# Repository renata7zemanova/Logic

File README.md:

# Elektronická hra Logic

Elektronická hra Logic je hra, která je založena na principu deskové hry Logic.

## DPS

Deska plošného spoje je nakreslena v programu KiCad. 

## Software

Pro programování DPS Elektronické hry Logic je zapotřebí stáhnout a nainstalovat vývojové prostředí [Visual Studio Code](https://code.visualstudio.com/) a v něm rozšíření PlatformIO. 

Software je napsán pomocí Arduino frameworku.

Při programování musí být přepínač SW15 vždy dole (v pozici 1).

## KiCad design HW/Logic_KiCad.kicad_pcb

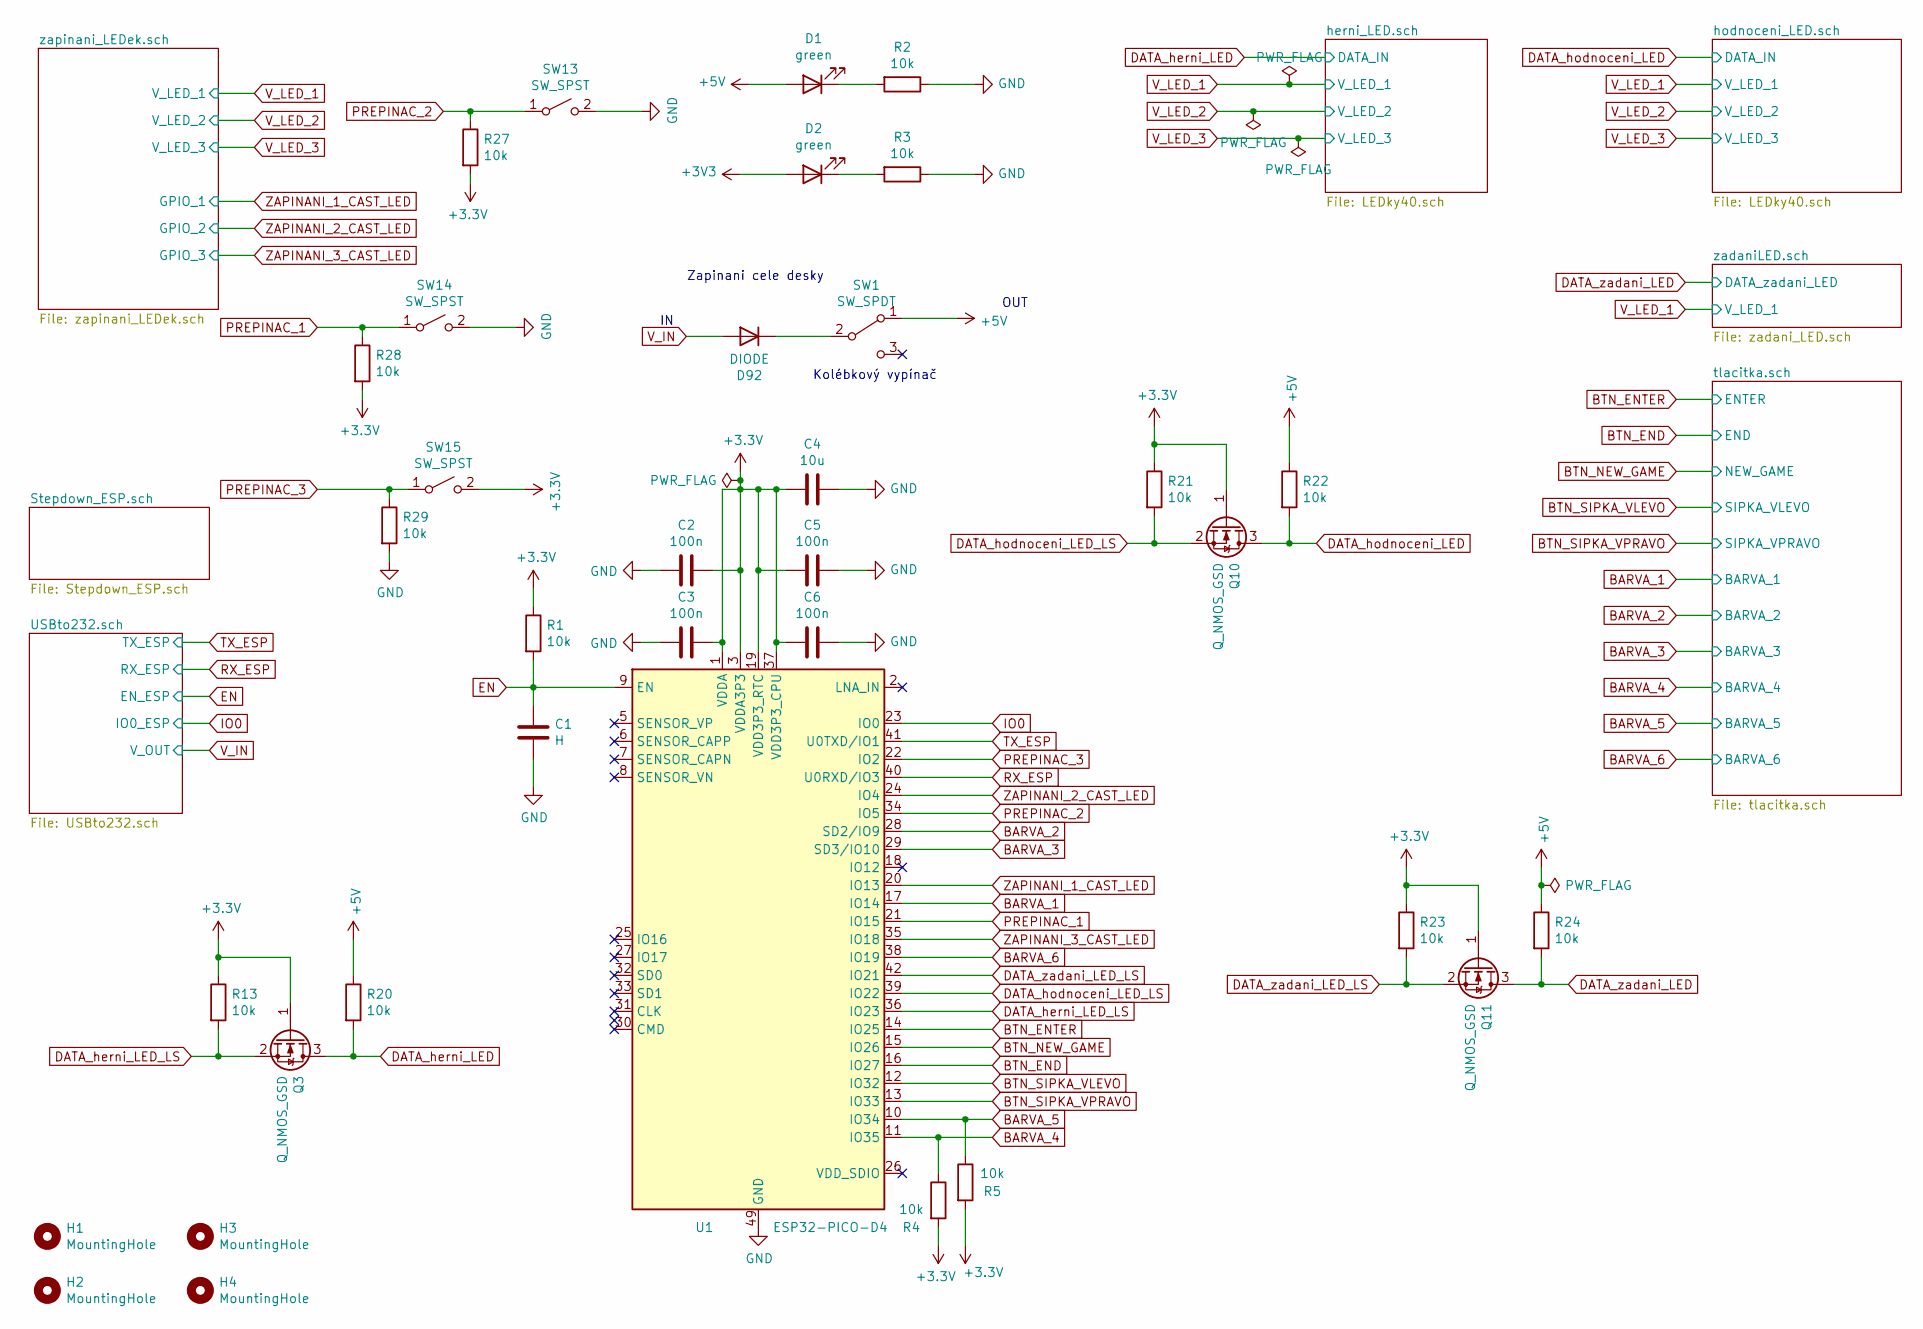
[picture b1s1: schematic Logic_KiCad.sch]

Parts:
C1: H; C_0402_1005Metric; LCSC C52923
C2, C3, C5, C6: 100n; C_0402_1005Metric; LCSC C1525
C4: 10u; C_0402_1005Metric; LCSC C15525
D1, D2: green; LED_0603_1608Metric; LCSC C72043
D92: DIODE; D_SMA; LCSC C8678
H1, H2, H3, H4: MountingHole; MountingHole_3.2mm_M3_DIN965_Pad; JLCPCB_CORRECTION 0;0;0
Q3, Q10, Q11: Q_NMOS_GSD; SOT-23; LCSC C8545
R1, R2, R3, R4, R5, R13, R20, R21, R22, R23, R24, R27, R28, R29: 10k; R_0402_1005Metric; LCSC C25744
SW1: SW_SPDT; PinHeader_1x03_P2.54mm_Vertical; LCSC ručně
SW13: SW_SPST; DIP1x1; JLCPCB_CORRECTION 0;0;270
SW14, SW15: SW_SPST; DIP1x1; JLCPCB_CORRECTION 0;0;90
U1: ESP32-PICO-D4; QFN-48-1EP_7x7mm_P0.5mm_EP5.3x5.3mm; LCSC C193707

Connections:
+5V: D1.2 (A), R20.1, R22.1, R24.1, SW1.1 (A); also elsewhere on the board
BARVA_1: U1.17 (IO14); also elsewhere on the board
BARVA_2: U1.28 (SD2/IO9); also elsewhere on the board
BARVA_3: U1.29 (SD3/IO10); also elsewhere on the board
BARVA_4: R4.1, U1.11 (IO35); also elsewhere on the board
BARVA_5: R5.1, U1.10 (IO34); also elsewhere on the board
BARVA_6: U1.38 (IO19); also elsewhere on the board
BTN_END: U1.16 (IO27); also elsewhere on the board
BTN_ENTER: U1.14 (IO25); also elsewhere on the board
BTN_NEW_GAME: U1.15 (IO26); also elsewhere on the board
BTN_SIPKA_VLEVO: U1.12 (IO32); also elsewhere on the board
BTN_SIPKA_VPRAVO: U1.13 (IO33); also elsewhere on the board
DATA_herni_LED: Q3.3 (D), R20.2; also elsewhere on the board
DATA_herni_LED_LS: Q3.2 (S), R13.2, U1.36 (IO23)
DATA_hodnoceni_LED: Q10.3 (D), R22.2; also elsewhere on the board
DATA_hodnoceni_LED_LS: Q10.2 (S), R21.2, U1.39 (IO22)
DATA_zadani_LED: Q11.3 (D), R24.2; also elsewhere on the board
DATA_zadani_LED_LS: Q11.2 (S), R23.2, U1.42 (IO21)
EN: C1.2, R1.2, U1.9 (EN); also elsewhere on the board
GND: C1.1, C2.2, C3.2, C4.1, C5.1, C6.1, R2.1, R3.1, R29.2, SW13.2 (B), SW14.2 (B), U1.49 (GND); also elsewhere on the board
IO0: U1.23 (IO0); also elsewhere on the board
unnamed: D1.1 (K), R2.2
unnamed: D2.1 (K), R3.2
unnamed: D92.1 (K), SW1.2 (B)
PREPINAC_1: R28.1, SW14.1 (A), U1.21 (IO15)
PREPINAC_2: R27.1, SW13.1 (A), U1.34 (IO5)
PREPINAC_3: R29.1, SW15.1 (A), U1.22 (IO2)
RX_ESP: U1.40 (U0RXD/IO3); also elsewhere on the board
TX_ESP: U1.41 (U0TXD/IO1); also elsewhere on the board
V_IN: D92.2 (A); also elsewhere on the board
ZAPINANI_1_CAST_LED: U1.20 (IO13); also elsewhere on the board
ZAPINANI_2_CAST_LED: U1.24 (IO4); also elsewhere on the board
ZAPINANI_3_CAST_LED: U1.35 (IO18); also elsewhere on the board

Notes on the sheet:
Zapinani cele desky
Kolébkový vypínač
OUT

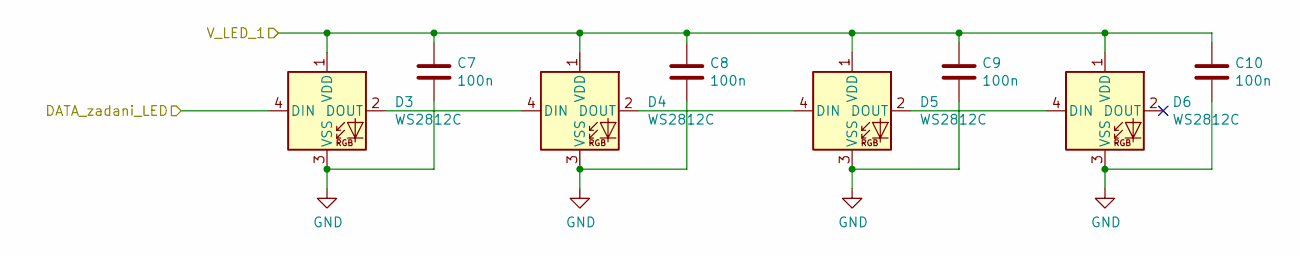
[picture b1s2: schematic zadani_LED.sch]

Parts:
C7, C8, C9, C10: 100n; C_0402_1005Metric; LCSC C1525
D3, D4, D5, D6: WS2812C; LED_WS2812B_PLCC4_5.0x5.0mm_P3.2mm; LCSC C114587

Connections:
DATA_zadani_LED: D3.4 (DIN); also elsewhere on the board
GND: C7.2, C8.2, C9.2, C10.2, D3.3 (VSS), D4.3 (VSS), D5.3 (VSS), D6.3 (VSS); also elsewhere on the board
unnamed: D3.2 (DOUT), D4.4 (DIN)
unnamed: D4.2 (DOUT), D5.4 (DIN)
unnamed: D5.2 (DOUT), D6.4 (DIN)
V_LED_1: C7.1, C8.1, C9.1, C10.1, D3.1 (VDD), D4.1 (VDD), D5.1 (VDD), D6.1 (VDD); also elsewhere on the board

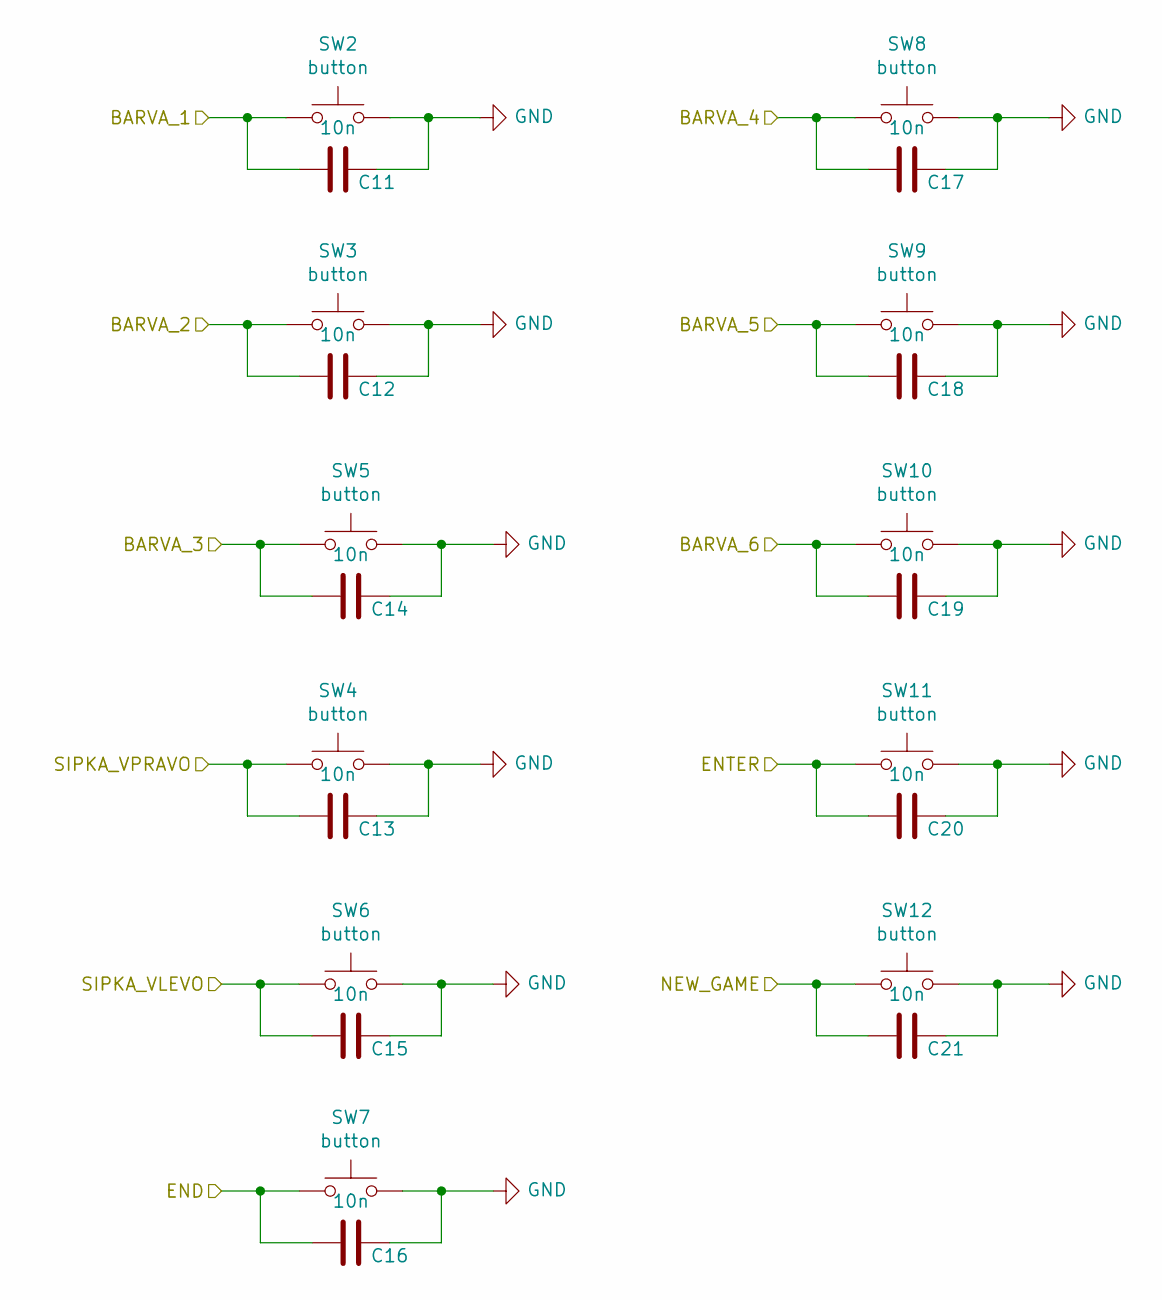
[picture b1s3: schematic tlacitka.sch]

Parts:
C11, C12, C13, C14, C15, C16, C17, C18, C19, C20, C21: 10n; C_0402_1005Metric; LCSC C15195
SW2, SW3, SW4, SW5, SW6, SW7, SW8, SW9, SW10, SW11, SW12: button; Tactile_switch; LCSC C318886

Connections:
BARVA_1: C11.2, SW2.1; also elsewhere on the board
BARVA_2: C12.2, SW3.1; also elsewhere on the board
BARVA_3: C14.2, SW5.1; also elsewhere on the board
BARVA_4: C17.2, SW8.1; also elsewhere on the board
BARVA_5: C18.2, SW9.1; also elsewhere on the board
BARVA_6: C19.2, SW10.1; also elsewhere on the board
BTN_END: C16.2, SW7.1; also elsewhere on the board
BTN_ENTER: C20.2, SW11.1; also elsewhere on the board
BTN_NEW_GAME: C21.2, SW12.1; also elsewhere on the board
BTN_SIPKA_VLEVO: C15.2, SW6.1; also elsewhere on the board
BTN_SIPKA_VPRAVO: C13.2, SW4.1; also elsewhere on the board
GND: C11.1, C12.1, C13.1, C14.1, C15.1, C16.1, C17.1, C18.1, C19.1, C20.1, C21.1, SW2.2, SW3.2, SW4.2, SW5.2, SW6.2, SW7.2, SW8.2, SW9.2, SW10.2, SW11.2, SW12.2; also elsewhere on the board

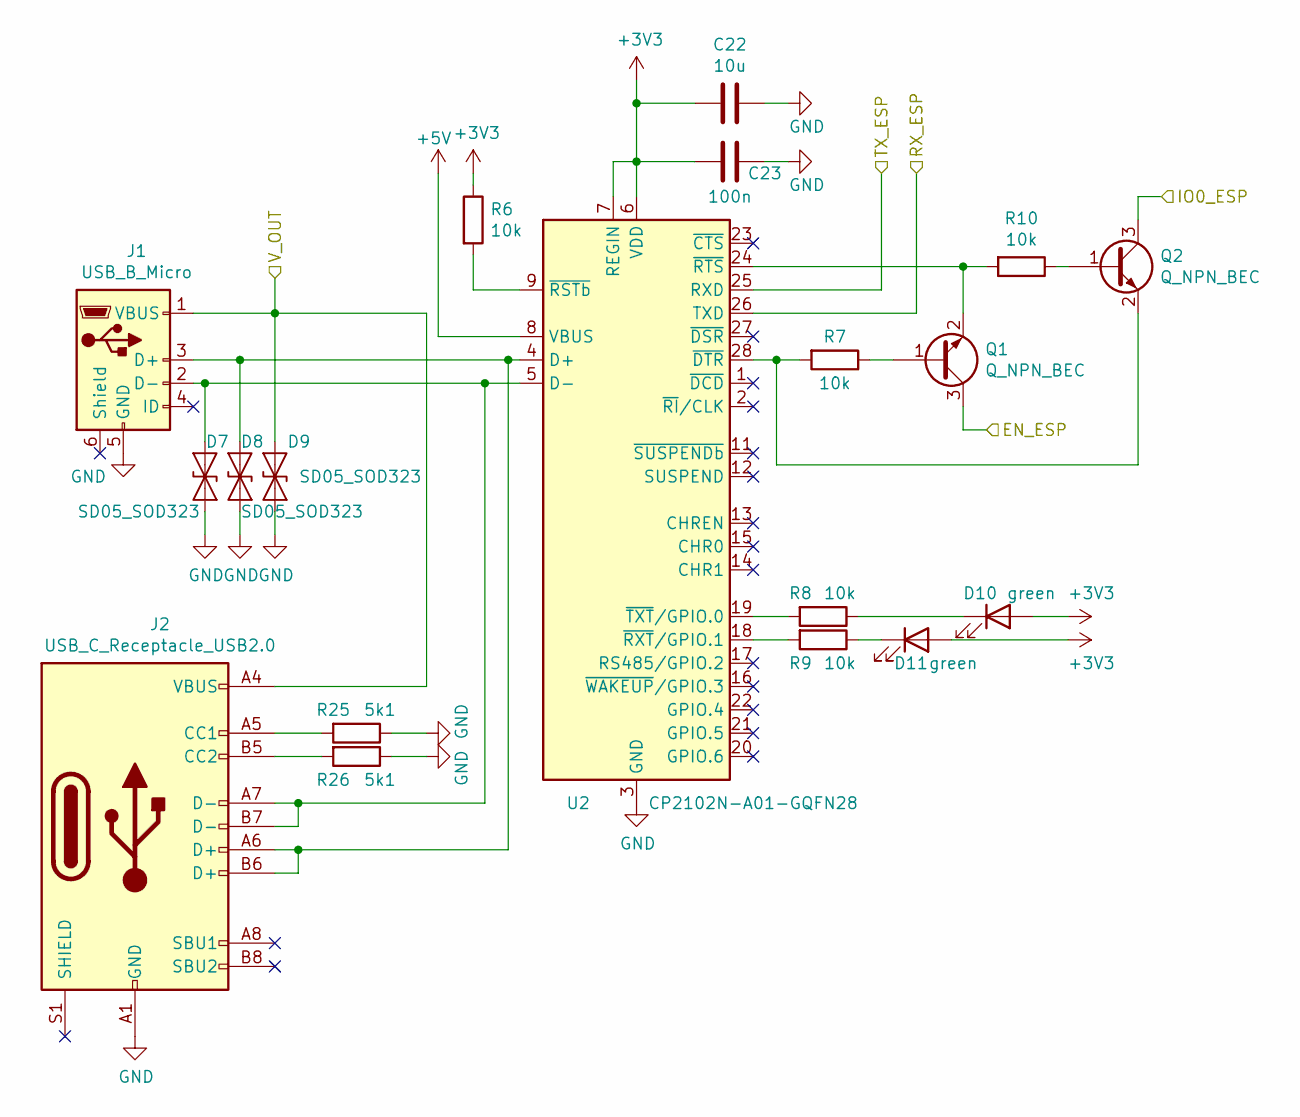
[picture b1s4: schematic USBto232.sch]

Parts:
C22: 10u; C_0402_1005Metric; LCSC C15525
C23: 100n; C_0402_1005Metric; LCSC C1525
D7, D8, D9: SD05_SOD323; D_SOD-323; LCSC neosazovat
D10, D11: green; LED_0603_1608Metric; LCSC C72043
J1: USB_B_Micro; USB_Micro-B_Wuerth_629105150521; LCSC C319164
J2: USB_C_Receptacle_USB2.0; USB_C_Receptacle_HRO_TYPE-C-31-M-12; JLCPCB_CORRECTION 1.8;0;180
Q1, Q2: Q_NPN_BEC; SOT-23; LCSC C20526
R6, R7, R8, R9, R10: 10k; R_0402_1005Metric; LCSC C25744
R25, R26: 5k1; R_0402_1005Metric; JLCPCB_CORRECTION 0;0;0
U2: CP2102N-A01-GQFN28; QFN-28-1EP_5x5mm_P0.5mm_EP3.35x3.35mm; LCSC C6568

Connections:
+5V: U2.8 (VBUS); also elsewhere on the board
EN: Q1.3 (C); also elsewhere on the board
GND: C22.1, C23.1, D7.1 (A1), D8.1 (A1), D9.1 (A1), J1.5 (GND), J2.A1 (GND), J2.A12 (GND), J2.B1 (GND), J2.B12 (GND), R25.1, R26.1, U2.3 (GND), U2.29 (GND); also elsewhere on the board
IO0: Q2.3 (C); also elsewhere on the board
unnamed: D7.2 (A2), J1.2 (D-), J2.A7 (D-), J2.B7 (D-), U2.5 (D-)
unnamed: D8.2 (A2), J1.3 (D+), J2.A6 (D+), J2.B6 (D+), U2.4 (D+)
unnamed: D10.1 (K), R8.1
unnamed: D11.1 (K), R9.1
unnamed: J2.A5 (CC1), R25.2
unnamed: J2.B5 (CC2), R26.2
unnamed: Q1.1 (B), R7.1
unnamed: Q1.2 (E), R10.2, U2.24 (~RTS)
unnamed: Q2.1 (B), R10.1
unnamed: Q2.2 (E), R7.2, U2.28 (~DTR)
unnamed: R6.2, U2.9 (~RSTb)
unnamed: R8.2, U2.19 (~TXT~/GPIO.0)
unnamed: R9.2, U2.18 (~RXT~/GPIO.1)
RX_ESP: U2.26 (TXD); also elsewhere on the board
TX_ESP: U2.25 (RXD); also elsewhere on the board
V_IN: D9.2 (A2), J1.1 (VBUS), J2.A4 (VBUS), J2.A9 (VBUS), J2.B4 (VBUS), J2.B9 (VBUS); also elsewhere on the board

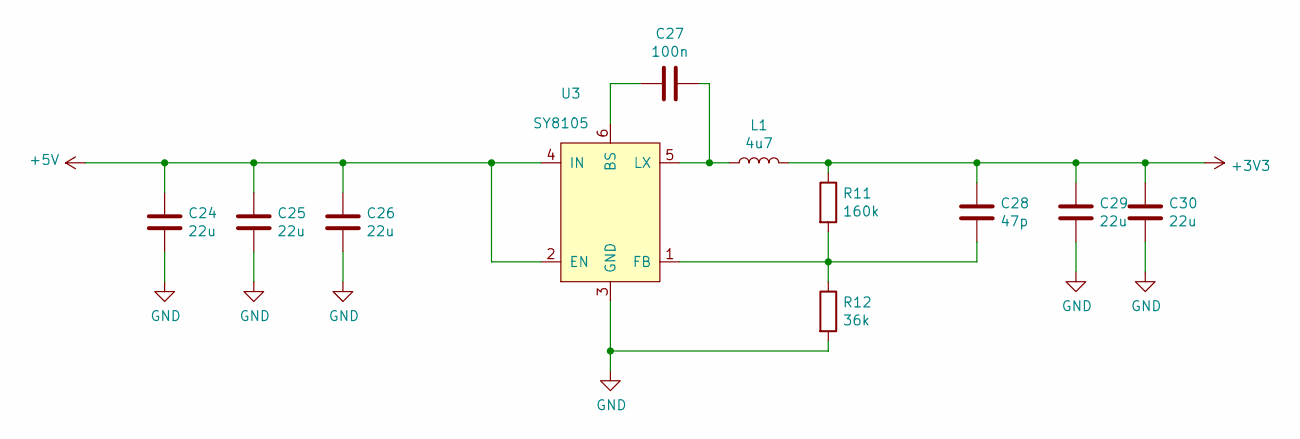
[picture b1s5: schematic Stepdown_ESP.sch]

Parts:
C24, C25, C26, C29, C30: 22u; C_0603_1608Metric; LCSC C59461
C27: 100n; C_0402_1005Metric; LCSC C1525
C28: 47p; C_0402_1005Metric; LCSC C1567
L1: 4u7; MWSA0503S; LCSC C408410
R11: 160k; R_0603_1608Metric; LCSC C22813
R12: 36k; R_0603_1608Metric; LCSC C23147
U3: SY8105; TSOT-23-6; LCSC C178247

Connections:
+5V: C24.1, C25.1, C26.1, U3.2 (EN), U3.4 (IN); also elsewhere on the board
GND: C24.2, C25.2, C26.2, C29.1, C30.1, R12.2, U3.3 (GND); also elsewhere on the board
unnamed: C27.1, L1.1, U3.5 (LX)
unnamed: C27.2, U3.6 (BS)
unnamed: C28.1, R11.2, R12.1, U3.1 (FB)

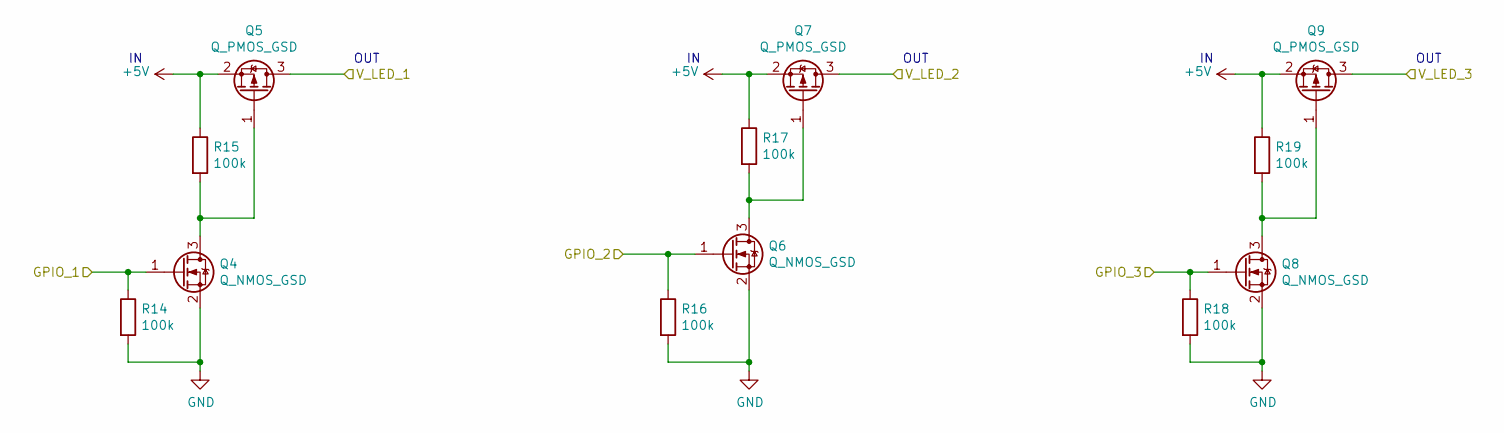
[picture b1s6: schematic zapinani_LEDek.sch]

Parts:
Q4, Q6, Q8: Q_NMOS_GSD; SOT-23; LCSC C8545
Q5, Q7, Q9: Q_PMOS_GSD; SOT-23; LCSC C10487
R14, R15, R16, R17, R18, R19: 100k; R_0402_1005Metric; LCSC C25741

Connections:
+5V: Q5.2 (S), Q7.2 (S), Q9.2 (S), R15.1, R17.1, R19.1; also elsewhere on the board
GND: Q4.2 (S), Q6.2 (S), Q8.2 (S), R14.2, R16.2, R18.2; also elsewhere on the board
unnamed: Q4.3 (D), Q5.1 (G), R15.2
unnamed: Q6.3 (D), Q7.1 (G), R17.2
unnamed: Q8.3 (D), Q9.1 (G), R19.2
V_LED_1: Q5.3 (D); also elsewhere on the board
V_LED_2: Q7.3 (D); also elsewhere on the board
V_LED_3: Q9.3 (D); also elsewhere on the board
ZAPINANI_1_CAST_LED: Q4.1 (G), R14.1; also elsewhere on the board
ZAPINANI_2_CAST_LED: Q6.1 (G), R16.1; also elsewhere on the board
ZAPINANI_3_CAST_LED: Q8.1 (G), R18.1; also elsewhere on the board

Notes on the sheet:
OUT

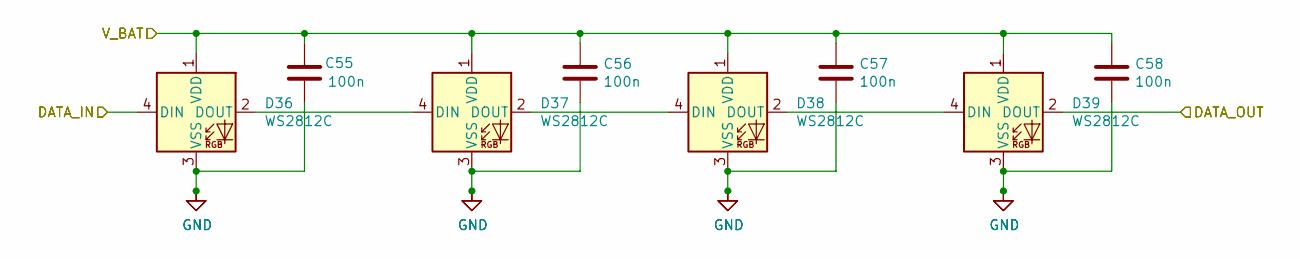
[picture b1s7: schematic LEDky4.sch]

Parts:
C75, C76, C77, C78: 100n; C_0402_1005Metric; LCSC C1525
D56, D57, D58, D59: WS2812C; LED_WS2812B_PLCC4_5.0x5.0mm_P3.2mm; LCSC C114587

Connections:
/hodnoceni_LED.sch/2.sch/DATA_IN: D56.4 (DIN); also elsewhere on the board
/hodnoceni_LED.sch/3.sch/DATA_IN: D59.2 (DOUT); also elsewhere on the board
GND: C75.2, C76.2, C77.2, C78.2, D56.3 (VSS), D57.3 (VSS), D58.3 (VSS), D59.3 (VSS); also elsewhere on the board
unnamed: D56.2 (DOUT), D57.4 (DIN)
unnamed: D57.2 (DOUT), D58.4 (DIN)
unnamed: D58.2 (DOUT), D59.4 (DIN)
V_LED_1: C75.1, C76.1, C77.1, C78.1, D56.1 (VDD), D57.1 (VDD), D58.1 (VDD), D59.1 (VDD); also elsewhere on the board

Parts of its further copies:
C31, C32, C33, C34, C35, C36, C37, C38, C39, C40, C41, C42, C43, C44, C45, C46, C47, C48, C49, C50, C51, C52, C53, C54, C55, C56, C57, C58, C59, C60, C61, C62, C63, C64, C65, C66, C67, C68, C69, C70, C71, C72, C73, C74, C79, C80, C81, C82, C83, C84, C85, C86, C87, C88, C89, C90, C91, C92, C93, C94, C95, C96, C97, C98, C99, C100, C101, C102, C103, C104, C105, C106, C107, C108, C109, C110: 100n; C_0402_1005Metric; LCSC C1525
D12, D13, D14, D15, D16, D17, D18, D19, D20, D21, D22, D23, D24, D25, D26, D27, D28, D29, D30, D31, D32, D33, D34, D35, D36, D37, D38, D39, D40, D41, D42, D43, D44, D45, D46, D47, D48, D49, D50, D51, D52, D53, D54, D55, D60, D61, D62, D63, D64, D65, D66, D67, D68, D69, D70, D71, D72, D73, D74, D75, D76, D77, D78, D79, D80, D81, D82, D83, D84, D85, D86, D87, D88, D89, D90, D91: WS2812C; LED_WS2812B_PLCC4_5.0x5.0mm_P3.2mm; LCSC C114587

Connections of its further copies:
/herni_LED.sch/2.sch/DATA_IN: D15.2 (DOUT), D16.4 (DIN)
/herni_LED.sch/3.sch/DATA_IN: D19.2 (DOUT), D20.4 (DIN)
/herni_LED.sch/4.ch/DATA_IN: D23.2 (DOUT), D24.4 (DIN)
/herni_LED.sch/5.sch/DATA_IN: D27.2 (DOUT), D28.4 (DIN)
/herni_LED.sch/6.sch/DATA_IN: D31.2 (DOUT), D32.4 (DIN)
/herni_LED.sch/7.sch/DATA_IN: D35.2 (DOUT), D36.4 (DIN)
/herni_LED.sch/8.sch/DATA_IN: D39.2 (DOUT), D40.4 (DIN)
/herni_LED.sch/9.sch/DATA_IN: D43.2 (DOUT), D44.4 (DIN)
/herni_LED.sch/10.sch/DATA_IN: D47.2 (DOUT), D48.4 (DIN)
/herni_LED.sch/10.sch/DATA_OUT: D51.2 (DOUT)
/hodnoceni_LED.sch/2.sch/DATA_IN: D55.2 (DOUT); also elsewhere on the board
/hodnoceni_LED.sch/3.sch/DATA_IN: D60.4 (DIN); also elsewhere on the board
/hodnoceni_LED.sch/4.ch/DATA_IN: D63.2 (DOUT), D64.4 (DIN)
/hodnoceni_LED.sch/5.sch/DATA_IN: D67.2 (DOUT), D68.4 (DIN)
/hodnoceni_LED.sch/6.sch/DATA_IN: D71.2 (DOUT), D72.4 (DIN)
/hodnoceni_LED.sch/7.sch/DATA_IN: D75.2 (DOUT), D76.4 (DIN)
/hodnoceni_LED.sch/8.sch/DATA_IN: D79.2 (DOUT), D80.4 (DIN)
/hodnoceni_LED.sch/9.sch/DATA_IN: D83.2 (DOUT), D84.4 (DIN)
/hodnoceni_LED.sch/10.sch/DATA_IN: D87.2 (DOUT), D88.4 (DIN)
/hodnoceni_LED.sch/10.sch/DATA_OUT: D91.2 (DOUT)
DATA_herni_LED: D12.4 (DIN); also elsewhere on the board
DATA_hodnoceni_LED: D52.4 (DIN); also elsewhere on the board
GND: C31.2, C32.2, C33.2, C34.2, C35.2, C36.2, C37.2, C38.2, C39.2, C40.2, C41.2, C42.2, C43.2, C44.2, C45.2, C46.2, C47.2, C48.2, C49.2, C50.2, C51.2, C52.2, C53.2, C54.2, C55.2, C56.2, C57.2, C58.2, C59.2, C60.2, C61.2, C62.2, C63.2, C64.2, C65.2, C66.2, C67.2, C68.2, C69.2, C70.2, C71.2, C72.2, C73.2, C74.2, C79.2, C80.2, C81.2, C82.2, C83.2, C84.2, C85.2, C86.2, C87.2, C88.2, C89.2, C90.2, C91.2, C92.2, C93.2, C94.2, C95.2, C96.2, C97.2, C98.2, C99.2, C100.2, C101.2, C102.2, C103.2, C104.2, C105.2, C106.2, C107.2, C108.2, C109.2, C110.2, D12.3 (VSS), D13.3 (VSS), D14.3 (VSS), D15.3 (VSS), D16.3 (VSS), D17.3 (VSS), D18.3 (VSS), D19.3 (VSS), D20.3 (VSS), D21.3 (VSS), D22.3 (VSS), D23.3 (VSS), D24.3 (VSS), D25.3 (VSS), D26.3 (VSS), D27.3 (VSS), D28.3 (VSS), D29.3 (VSS), D30.3 (VSS), D31.3 (VSS), D32.3 (VSS), D33.3 (VSS), D34.3 (VSS), D35.3 (VSS), D36.3 (VSS), D37.3 (VSS), D38.3 (VSS), D39.3 (VSS), D40.3 (VSS), D41.3 (VSS), D42.3 (VSS), D43.3 (VSS), D44.3 (VSS), D45.3 (VSS), D46.3 (VSS), D47.3 (VSS), D48.3 (VSS), D49.3 (VSS), D50.3 (VSS), D51.3 (VSS), D52.3 (VSS), D53.3 (VSS), D54.3 (VSS), D55.3 (VSS), D60.3 (VSS), D61.3 (VSS), D62.3 (VSS), D63.3 (VSS), D64.3 (VSS), D65.3 (VSS), D66.3 (VSS), D67.3 (VSS), D68.3 (VSS), D69.3 (VSS), D70.3 (VSS), D71.3 (VSS), D72.3 (VSS), D73.3 (VSS), D74.3 (VSS), D75.3 (VSS), D76.3 (VSS), D77.3 (VSS), D78.3 (VSS), D79.3 (VSS), D80.3 (VSS), D81.3 (VSS), D82.3 (VSS), D83.3 (VSS), D84.3 (VSS), D85.3 (VSS), D86.3 (VSS), D87.3 (VSS), D88.3 (VSS), D89.3 (VSS), D90.3 (VSS), D91.3 (VSS); also elsewhere on the board
unnamed: D12.2 (DOUT), D13.4 (DIN)
unnamed: D13.2 (DOUT), D14.4 (DIN)
unnamed: D14.2 (DOUT), D15.4 (DIN)
unnamed: D16.2 (DOUT), D17.4 (DIN)
unnamed: D17.2 (DOUT), D18.4 (DIN)
unnamed: D18.2 (DOUT), D19.4 (DIN)
unnamed: D20.2 (DOUT), D21.4 (DIN)
unnamed: D21.2 (DOUT), D22.4 (DIN)
unnamed: D22.2 (DOUT), D23.4 (DIN)
unnamed: D24.2 (DOUT), D25.4 (DIN)
unnamed: D25.2 (DOUT), D26.4 (DIN)
unnamed: D26.2 (DOUT), D27.4 (DIN)
unnamed: D28.2 (DOUT), D29.4 (DIN)
unnamed: D29.2 (DOUT), D30.4 (DIN)
unnamed: D30.2 (DOUT), D31.4 (DIN)
unnamed: D32.2 (DOUT), D33.4 (DIN)
unnamed: D33.2 (DOUT), D34.4 (DIN)
unnamed: D34.2 (DOUT), D35.4 (DIN)
unnamed: D36.2 (DOUT), D37.4 (DIN)
unnamed: D37.2 (DOUT), D38.4 (DIN)
unnamed: D38.2 (DOUT), D39.4 (DIN)
unnamed: D40.2 (DOUT), D41.4 (DIN)
unnamed: D41.2 (DOUT), D42.4 (DIN)
unnamed: D42.2 (DOUT), D43.4 (DIN)
unnamed: D44.2 (DOUT), D45.4 (DIN)
unnamed: D45.2 (DOUT), D46.4 (DIN)
unnamed: D46.2 (DOUT), D47.4 (DIN)
unnamed: D48.2 (DOUT), D49.4 (DIN)
unnamed: D49.2 (DOUT), D50.4 (DIN)
unnamed: D50.2 (DOUT), D51.4 (DIN)
unnamed: D52.2 (DOUT), D53.4 (DIN)
unnamed: D53.2 (DOUT), D54.4 (DIN)
unnamed: D54.2 (DOUT), D55.4 (DIN)
unnamed: D60.2 (DOUT), D61.4 (DIN)
unnamed: D61.2 (DOUT), D62.4 (DIN)
unnamed: D62.2 (DOUT), D63.4 (DIN)
unnamed: D64.2 (DOUT), D65.4 (DIN)
unnamed: D65.2 (DOUT), D66.4 (DIN)
unnamed: D66.2 (DOUT), D67.4 (DIN)
unnamed: D68.2 (DOUT), D69.4 (DIN)
unnamed: D69.2 (DOUT), D70.4 (DIN)
unnamed: D70.2 (DOUT), D71.4 (DIN)
unnamed: D72.2 (DOUT), D73.4 (DIN)
unnamed: D73.2 (DOUT), D74.4 (DIN)
unnamed: D74.2 (DOUT), D75.4 (DIN)
unnamed: D76.2 (DOUT), D77.4 (DIN)
unnamed: D77.2 (DOUT), D78.4 (DIN)
unnamed: D78.2 (DOUT), D79.4 (DIN)
unnamed: D80.2 (DOUT), D81.4 (DIN)
unnamed: D81.2 (DOUT), D82.4 (DIN)
unnamed: D82.2 (DOUT), D83.4 (DIN)
unnamed: D84.2 (DOUT), D85.4 (DIN)
unnamed: D85.2 (DOUT), D86.4 (DIN)
unnamed: D86.2 (DOUT), D87.4 (DIN)
unnamed: D88.2 (DOUT), D89.4 (DIN)
unnamed: D89.2 (DOUT), D90.4 (DIN)
unnamed: D90.2 (DOUT), D91.4 (DIN)
V_LED_1: C31.1, C32.1, C33.1, C34.1, C35.1, C36.1, C37.1, C38.1, C39.1, C40.1, C41.1, C42.1, C43.1, C44.1, C45.1, C46.1, C71.1, C72.1, C73.1, C74.1, C79.1, C80.1, C81.1, C82.1, C83.1, C84.1, C85.1, C86.1, D12.1 (VDD), D13.1 (VDD), D14.1 (VDD), D15.1 (VDD), D16.1 (VDD), D17.1 (VDD), D18.1 (VDD), D19.1 (VDD), D20.1 (VDD), D21.1 (VDD), D22.1 (VDD), D23.1 (VDD), D24.1 (VDD), D25.1 (VDD), D26.1 (VDD), D27.1 (VDD), D52.1 (VDD), D53.1 (VDD), D54.1 (VDD), D55.1 (VDD), D60.1 (VDD), D61.1 (VDD), D62.1 (VDD), D63.1 (VDD), D64.1 (VDD), D65.1 (VDD), D66.1 (VDD), D67.1 (VDD); also elsewhere on the board
V_LED_2: C47.1, C48.1, C49.1, C50.1, C51.1, C52.1, C53.1, C54.1, C55.1, C56.1, C57.1, C58.1, C87.1, C88.1, C89.1, C90.1, C91.1, C92.1, C93.1, C94.1, C95.1, C96.1, C97.1, C98.1, D28.1 (VDD), D29.1 (VDD), D30.1 (VDD), D31.1 (VDD), D32.1 (VDD), D33.1 (VDD), D34.1 (VDD), D35.1 (VDD), D36.1 (VDD), D37.1 (VDD), D38.1 (VDD), D39.1 (VDD), D68.1 (VDD), D69.1 (VDD), D70.1 (VDD), D71.1 (VDD), D72.1 (VDD), D73.1 (VDD), D74.1 (VDD), D75.1 (VDD), D76.1 (VDD), D77.1 (VDD), D78.1 (VDD), D79.1 (VDD); also elsewhere on the board
V_LED_3: C59.1, C60.1, C61.1, C62.1, C63.1, C64.1, C65.1, C66.1, C67.1, C68.1, C69.1, C70.1, C99.1, C100.1, C101.1, C102.1, C103.1, C104.1, C105.1, C106.1, C107.1, C108.1, C109.1, C110.1, D40.1 (VDD), D41.1 (VDD), D42.1 (VDD), D43.1 (VDD), D44.1 (VDD), D45.1 (VDD), D46.1 (VDD), D47.1 (VDD), D48.1 (VDD), D49.1 (VDD), D50.1 (VDD), D51.1 (VDD), D80.1 (VDD), D81.1 (VDD), D82.1 (VDD), D83.1 (VDD), D84.1 (VDD), D85.1 (VDD), D86.1 (VDD), D87.1 (VDD), D88.1 (VDD), D89.1 (VDD), D90.1 (VDD), D91.1 (VDD); also elsewhere on the board

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
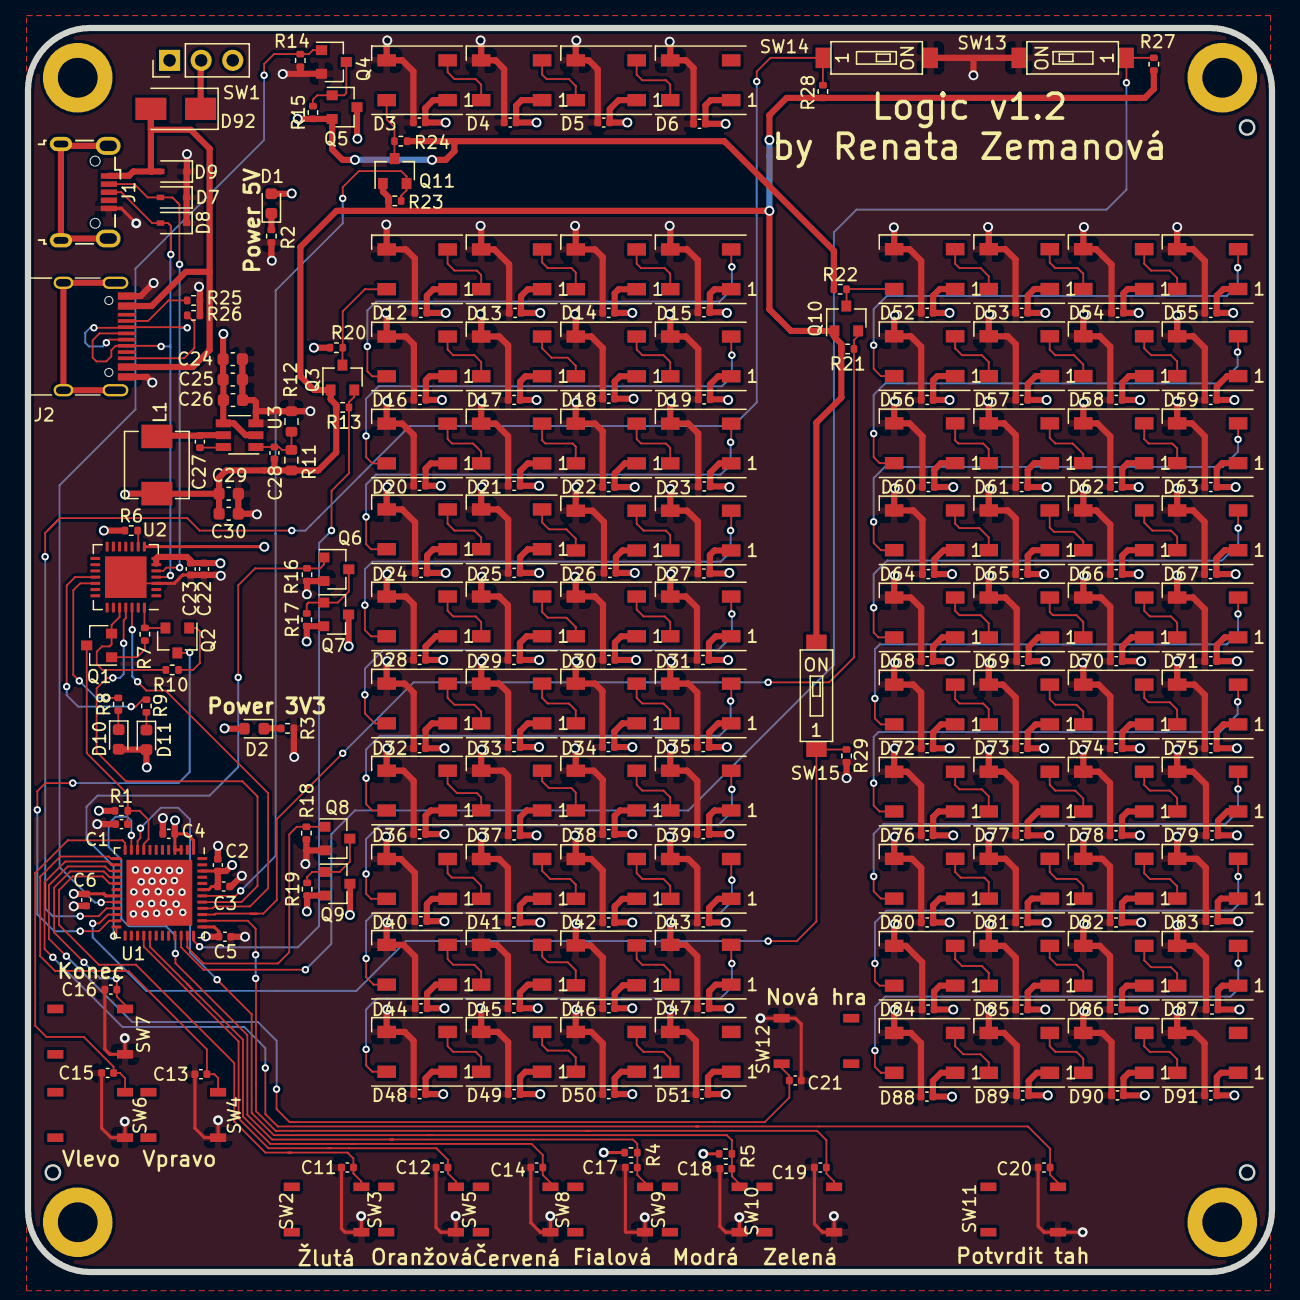
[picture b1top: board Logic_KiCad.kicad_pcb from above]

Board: 4 copper layers, 100.0 x 100.0 mm, 267 parts (0 on the bottom side), 137 nets.

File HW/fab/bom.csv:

Comment,Designator,Footprint,LCSC
ESP32-PICO-D4,U1,Package_DFN_QFN:QFN-48-1EP_7x7mm_P0.5mm_EP5.3x5.3mm,C193707
10k,"R1,R2,R3,R5,R4,R21,R22,R13,R20,R23,R24,R28,R27,R29,R6,R7,R10,R8,R9",Resistor_SMD:R_0402_1005Metric,C25744
H,C1,Capacitor_SMD:C_0402_1005Metric,C52923
10u,"C4,C22",Capacitor_SMD:C_0402_1005Metric,C15525
100n,"C6,C3,C2,C5,C7,C8,C9,C10,C23,C27,C31,C34,C32,C33,C35,C38,C36,C37,C39,C42,C40,C41,C43,C46,C44,C45,C47,C50,C48,C49,C51,C54,C52,C53,C55,C58,C56,C57,C59,C62,C60,C61,C63,C66,C64,C65,C67,C70,C68,C69,C71,C74,C72,C73,C75,C78,C76,C77,C79,C82,C80,C81,C83,C86,C84,C85,C87,C90,C88,C89,C91,C94,C92,C93,C95,C98,C96,C97,C99,C102,C100,C101,C103,C106,C104,C105,C107,C110,C108,C109",Capacitor_SMD:C_0402_1005Metric,C1525
green,"D1,D2,D10,D11",LED_SMD:LED_0603_1608Metric,C72043
DIODE,D92,Diode_SMD:D_SMA,C8678
Q_NMOS_GSD,"Q10,Q3,Q11,Q4,Q6,Q8",Package_TO_SOT_SMD:SOT-23,C8545
SW_SPST,"SW13,SW14,SW15",my_library:DIP1x1,C54948
WS2812C,"D3,D4,D5,D6,D13,D15,D12,D14,D17,D19,D16,D18,D21,D23,D20,D22,D25,D27,D24,D26,D29,D31,D28,D30,D33,D35,D32,D34,D37,D39,D36,D38,D41,D43,D40,D42,D45,D47,D44,D46,D49,D51,D48,D50,D53,D55,D52,D54,D57,D59,D56,D58,D61,D63,D60,D62,D65,D67,D64,D66,D69,D71,D68,D70,D73,D75,D72,D74,D77,D79,D76,D78,D81,D83,D80,D82,D85,D87,D84,D86,D89,D91,D88,D90",LED_SMD:LED_WS2812B_PLCC4_5.0x5.0mm_P3.2mm,C114587
10n,"C11,C16,C17,C19,C18,C14,C12,C21,C20,C15,C13",Capacitor_SMD:C_0402_1005Metric,C15195
button,"SW7,SW8,SW10,SW9,SW5,SW3,SW12,SW11,SW6,SW4,SW2",my_library:Tactile_switch,C318886
CP2102N-A01-GQFN28,U2,Package_DFN_QFN:QFN-28-1EP_5x5mm_P0.5mm_EP3.35x3.35mm,C6568
Q_NPN_BEC,"Q2,Q1",Package_TO_SOT_SMD:SOT-23,C20526
USB_C_Receptacle_USB2.0,J2,Connector_USB:USB_C_Receptacle_HRO_TYPE-C-31-M-12,C165948
5k1,"R25,R26",Resistor_SMD:R_0402_1005Metric,C25905
22u,"C24,C25,C26,C29,C30",Capacitor_SMD:C_0603_1608Metric,C59461
160k,R11,Resistor_SMD:R_0603_1608Metric,C22813
36k,R12,Resistor_SMD:R_0603_1608Metric,C23147
4u7,L1,my_library:MWSA0503S,C408410
47p,C28,Capacitor_SMD:C_0402_1005Metric,C1567
SY8105,U3,Package_TO_SOT_SMD:TSOT-23-6,C178247
100k,"R15,R17,R14,R16,R19,R18",Resistor_SMD:R_0402_1005Metric,C25741
Q_PMOS_GSD,"Q5,Q7,Q9",Package_TO_SOT_SMD:SOT-23,C10487
